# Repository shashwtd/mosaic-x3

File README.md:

## Mosaic X3

Imagine if github contribution chart came to life as a frame which you could hang on your wall for decor. This is mosaic, you plug it in, connect your github account and tadaaa~ you now have a frame that mimicks your github contribution history graph.

features:

- 84 blocks to display the last 12 weeks worth of stats
- wifi
- a programmable nfc tag for more accessiblity
- slim nice frame, designed so you can either hang this with a hanging rope, or using built in hooks behind the frame.
- clean white design, looks cool :yay:

### why

i wanted to make wall decor that felt personal and changed over time instead of being another static frame. my github contribution graph already represents the work i do, so turning it into a physical display felt like a fun mix of electronics, cad and code.

### how it was built

i designed the controller schematic and pcb in kicad around an esp32-s3. a 74ahct125 shifts the 3.3v data signal to 5v for the ws2812b leds. the 84 leds are arranged as a 12 x 7 grid inside a 3d printed enclosure, with an opal acrylic sheet in front to diffuse the light.

the bill of materials can be found [here](BOM.csv).

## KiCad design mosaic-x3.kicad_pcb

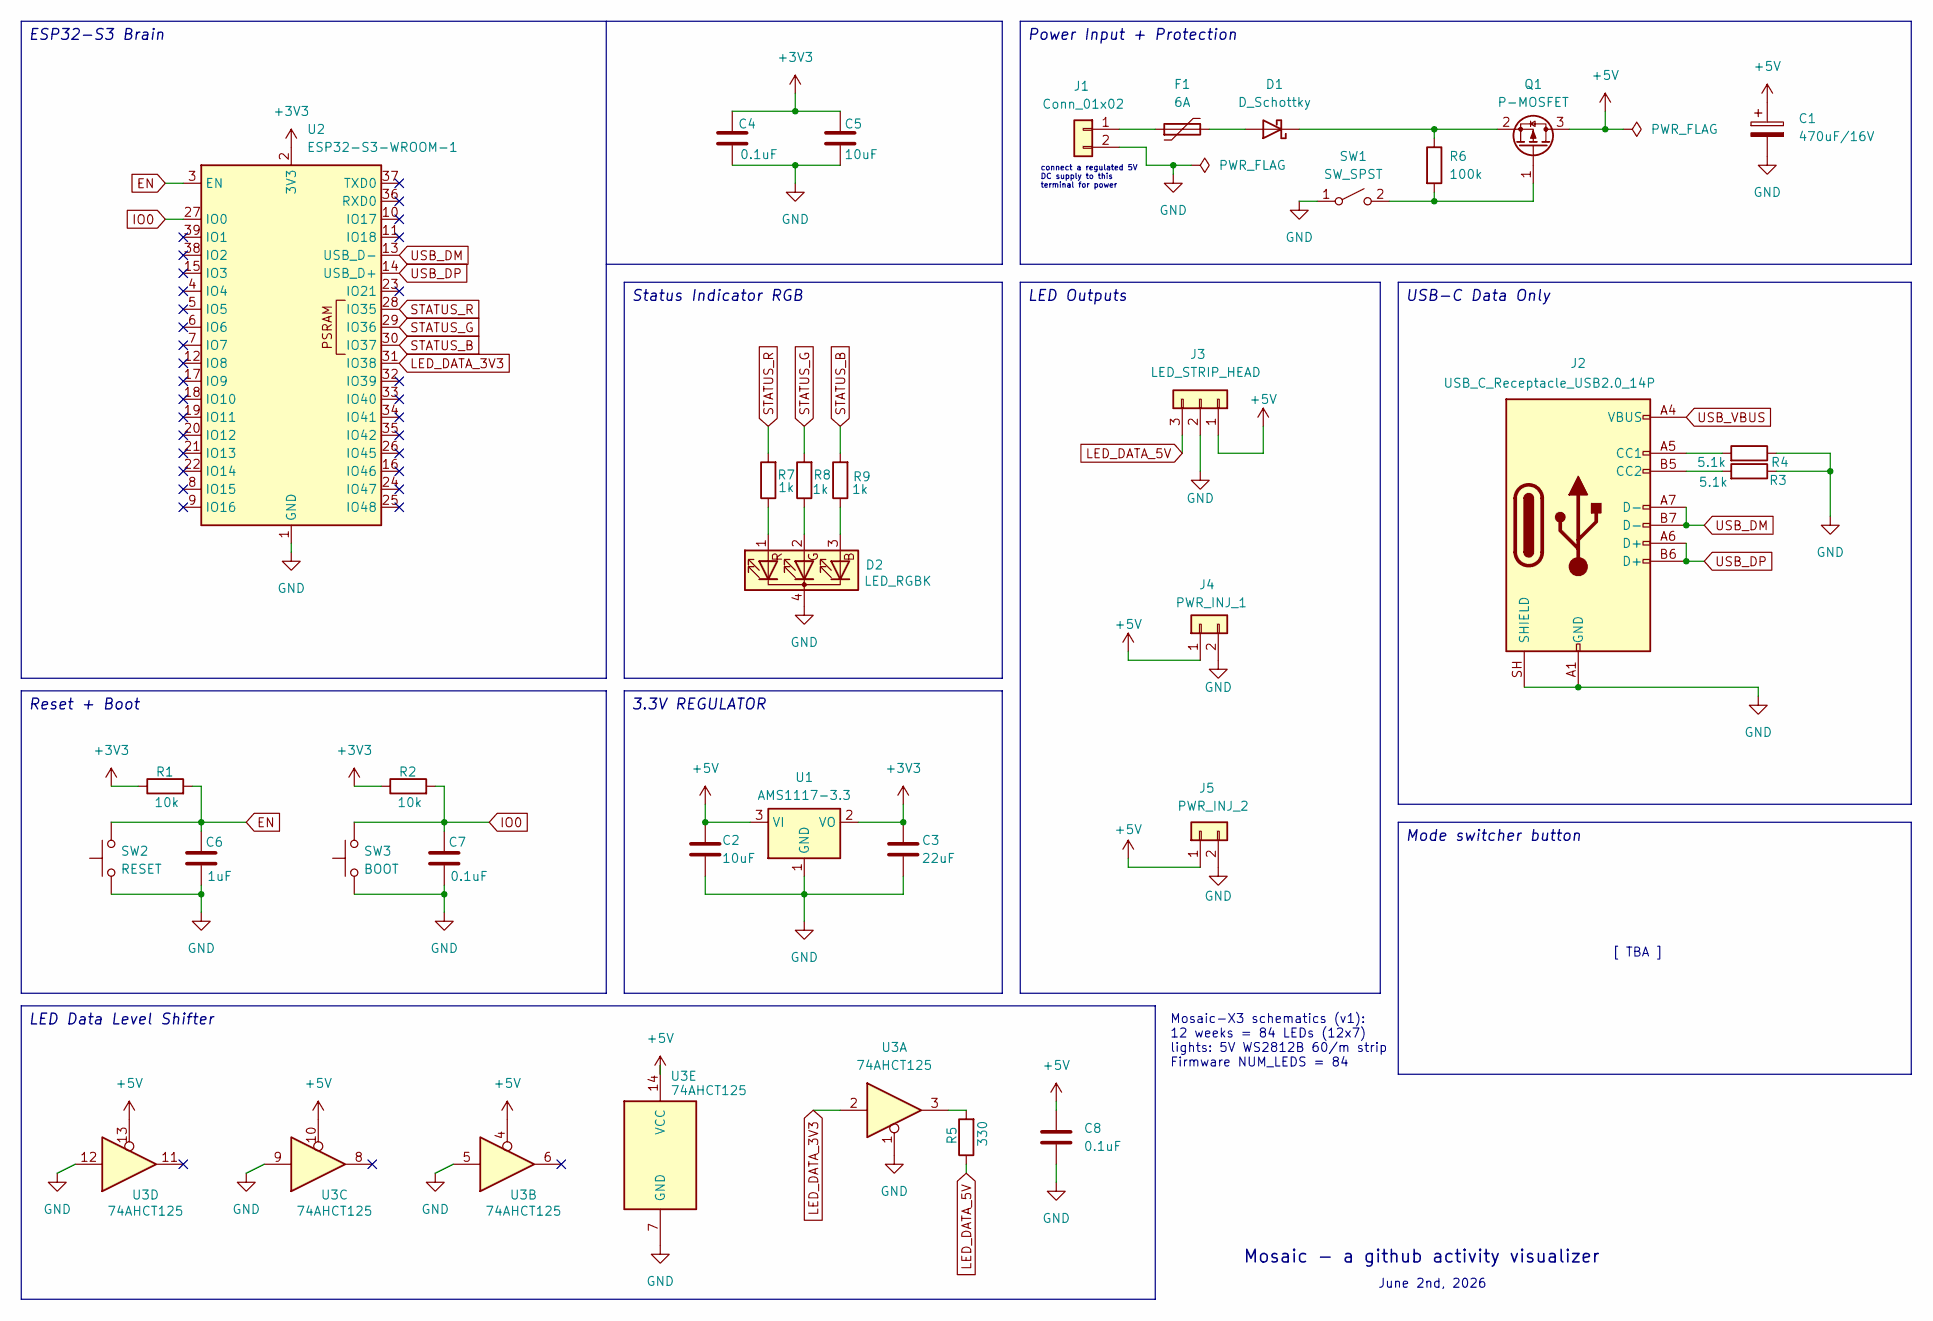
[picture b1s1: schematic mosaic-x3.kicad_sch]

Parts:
C1: 470uF/16V; CP_Radial_D8.0mm_P3.50mm
C2, C5: 10uF; C_0805_2012Metric
C3: 22uF; C_0805_2012Metric
C4, C7, C8: 0.1uF; C_0805_2012Metric
C6: 1uF; C_0805_2012Metric
D1: D_Schottky; D_SMA
D2: LED_RGBK; LED_D5.0mm-4_RGB
F1: 6A; Fuse_2920_7451Metric_Pad2.10x5.45mm_HandSolder
J1: Conn_01x02; TerminalBlock_Phoenix_MKDS-1-2-3.81_1x02_P3.81mm_Horizontal
J2: USB_C_Receptacle_USB2.0_14P; USB_C_Receptacle_HRO_TYPE-C-31-M-12
J3: LED_STRIP_HEAD; JST_XH_S3B-XH-A_1x03_P2.50mm_Horizontal
J4: PWR_INJ_1; JST_XH_S2B-XH-A_1x02_P2.50mm_Horizontal
J5: PWR_INJ_2; JST_XH_S2B-XH-A_1x02_P2.50mm_Horizontal
Q1: P-MOSFET; SOT-223-3_TabPin2
R1, R2: 10k; R_0805_2012Metric
R3, R4: 5.1k; R_0805_2012Metric
R5: 330; R_0805_2012Metric
R6: 100k; R_0805_2012Metric
R7, R8, R9: 1k; R_0805_2012Metric_Pad1.20x1.40mm_HandSolder
SW1: SW_SPST; SW_Slide_SPDT_Angled_CK_OS102011MA1Q
SW2: RESET; SW_SPST_SKQG_WithStem
SW3: BOOT; SW_SPST_SKQG_WithStem
U1: AMS1117-3.3; SOT-223-3_TabPin2
U2: ESP32-S3-WROOM-1
U3: 74AHCT125; SOIC-14_3.9x8.7mm_P1.27mm

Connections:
+3V3: C3.1, C4.1, C5.1, R1.1, R2.1, U1.2 (VO), U2.2 (3V3)
+5V: C1.1, C2.1, C8.1, J3.1, J4.1, J5.1, Q1.3 (D), U1.3 (VI), U3.4, U3.10, U3.13, U3.14 (VCC)
EN: C6.1, R1.2, SW2.2, U2.3 (EN)
GND: C1.2, C2.2, C3.2, C4.2, C5.2, C6.2, C7.2, C8.2, D2.4 (K), J1.2, J2.A1 (GND), J2.A12 (GND), J2.B1 (GND), J2.B12 (GND), J2.SH (SHIELD), J3.2, J4.2, J5.2, R3.1, R4.1, SW1.1 (A), SW2.1, SW3.1, U1.1 (GND), U2.1 (GND), U2.40 (GND), U2.41 (GND), U3.1, U3.5, U3.7 (GND), U3.9, U3.12
IO0: C7.1, R2.2, SW3.2, U2.27 (IO0)
LED_DATA_3V3: U2.31 (IO38), U3.2
LED_DATA_5V: J3.3, R5.1
unnamed: D1.2 (A), F1.2
unnamed: D1.1 (K), Q1.2 (S), R6.1
unnamed: D2.3 (BA), R9.1
unnamed: D2.2 (GA), R8.1
unnamed: D2.1 (RA), R7.1
unnamed: F1.1, J1.1
unnamed: J2.A5 (CC1), R4.2
unnamed: J2.B5 (CC2), R3.2
unnamed: Q1.1 (G), R6.2, SW1.2 (B)
unnamed: R5.2, U3.3
STATUS_B: R9.2, U2.30 (IO37)
STATUS_G: R8.2, U2.29 (IO36)
STATUS_R: R7.2, U2.28 (IO35)
USB_DM: J2.A7 (D-), J2.B7 (D-), U2.13 (USB_D-)
USB_DP: J2.A6 (D+), J2.B6 (D+), U2.14 (USB_D+)
USB_VBUS: J2.A4 (VBUS), J2.A9 (VBUS), J2.B4 (VBUS), J2.B9 (VBUS)

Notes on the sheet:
Mosaic - a github activity visualizer
[ TBA ]
connect a regulated 5V DC supply to this terminal for power
Mosaic-X3 schematics (v1): 12 weeks = 84 LEDs (12x7) lights: 5V WS2812B 60/m strip Firmware NUM_LEDS = 84
June 2nd, 2026
LED Data Level Shifter
Mode switcher button
USB-C Data Only
Reset + Boot
3.3V REGULATOR
Power Input + Protection
Status Indicator RGB
ESP32-S3 Brain
LED Outputs

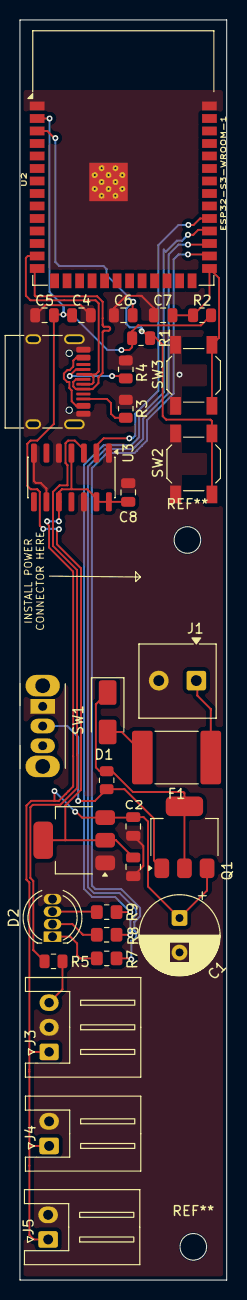
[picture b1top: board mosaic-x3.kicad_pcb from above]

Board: 2 copper layers, 21.0 x 128.0 mm, 32 parts (0 on the bottom side), 23 nets.

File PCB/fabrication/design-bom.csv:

"Designator","Comment","Footprint","Quantity","DNP"
"C1","470uF/16V","Capacitor_THT:CP_Radial_D8.0mm_P3.50mm","1",""
"C2,C5","10uF","Capacitor_SMD:C_0805_2012Metric","2",""
"C3","22uF","Capacitor_SMD:C_0805_2012Metric","1",""
"C4,C7,C8","0.1uF","Capacitor_SMD:C_0805_2012Metric","3",""
"C6","1uF","Capacitor_SMD:C_0805_2012Metric","1",""
"D1","D_Schottky","Diode_SMD:D_SMA","1",""
"D2","LED_RGBK","LED_THT:LED_D5.0mm-4_RGB","1",""
"F1","6A","Fuse:Fuse_2920_7451Metric_Pad2.10x5.45mm_HandSolder","1",""
"J1","Conn_01x02","TerminalBlock_Phoenix:TerminalBlock_Phoenix_MKDS-1-2-3.81_1x02_P3.81mm_Horizontal","1",""
"J2","USB_C_Receptacle_USB2.0_14P","Connector_USB:USB_C_Receptacle_HRO_TYPE-C-31-M-12","1",""
"J3","LED_STRIP_HEAD","Connector_JST:JST_XH_S3B-XH-A_1x03_P2.50mm_Horizontal","1",""
"J4","PWR_INJ_1","Connector_JST:JST_XH_S2B-XH-A_1x02_P2.50mm_Horizontal","1",""
"J5","PWR_INJ_2","Connector_JST:JST_XH_S2B-XH-A_1x02_P2.50mm_Horizontal","1",""
"Q1","P-MOSFET","Package_TO_SOT_SMD:SOT-223-3_TabPin2","1",""
"R1,R2","10k","Resistor_SMD:R_0805_2012Metric","2",""
"R3,R4","5.1k","Resistor_SMD:R_0805_2012Metric","2",""
"R5","330","Resistor_SMD:R_0805_2012Metric","1",""
"R6","100k","Resistor_SMD:R_0805_2012Metric","1",""
"R7-R9","1k","Resistor_SMD:R_0805_2012Metric_Pad1.20x1.40mm_HandSolder","3",""
"SW1","SW_SPST","Button_Switch_THT:SW_Slide_SPDT_Angled_CK_OS102011MA1Q","1",""
"SW2","RESET","Button_Switch_SMD:SW_SPST_SKQG_WithStem","1",""
"SW3","BOOT","Button_Switch_SMD:SW_SPST_SKQG_WithStem","1",""
"U1","AMS1117-3.3","Package_TO_SOT_SMD:SOT-223-3_TabPin2","1",""
"U2","ESP32-S3-WROOM-1","RF_Module:ESP32-S3-WROOM-1","1",""
"U3","74AHCT125","Package_SO:SOIC-14_3.9x8.7mm_P1.27mm","1",""

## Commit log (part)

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2026-06-02 updated project README
2026-06-03 schematic designs done
2026-06-04 update: working with footprints & PCB + added a 3d model for usb c
2026-06-08 updated schematic and fixed erc errors
2026-06-09 routed pcb and ran drc checks
2026-06-10 finished w the pcb board
2026-06-15 added an iamge
